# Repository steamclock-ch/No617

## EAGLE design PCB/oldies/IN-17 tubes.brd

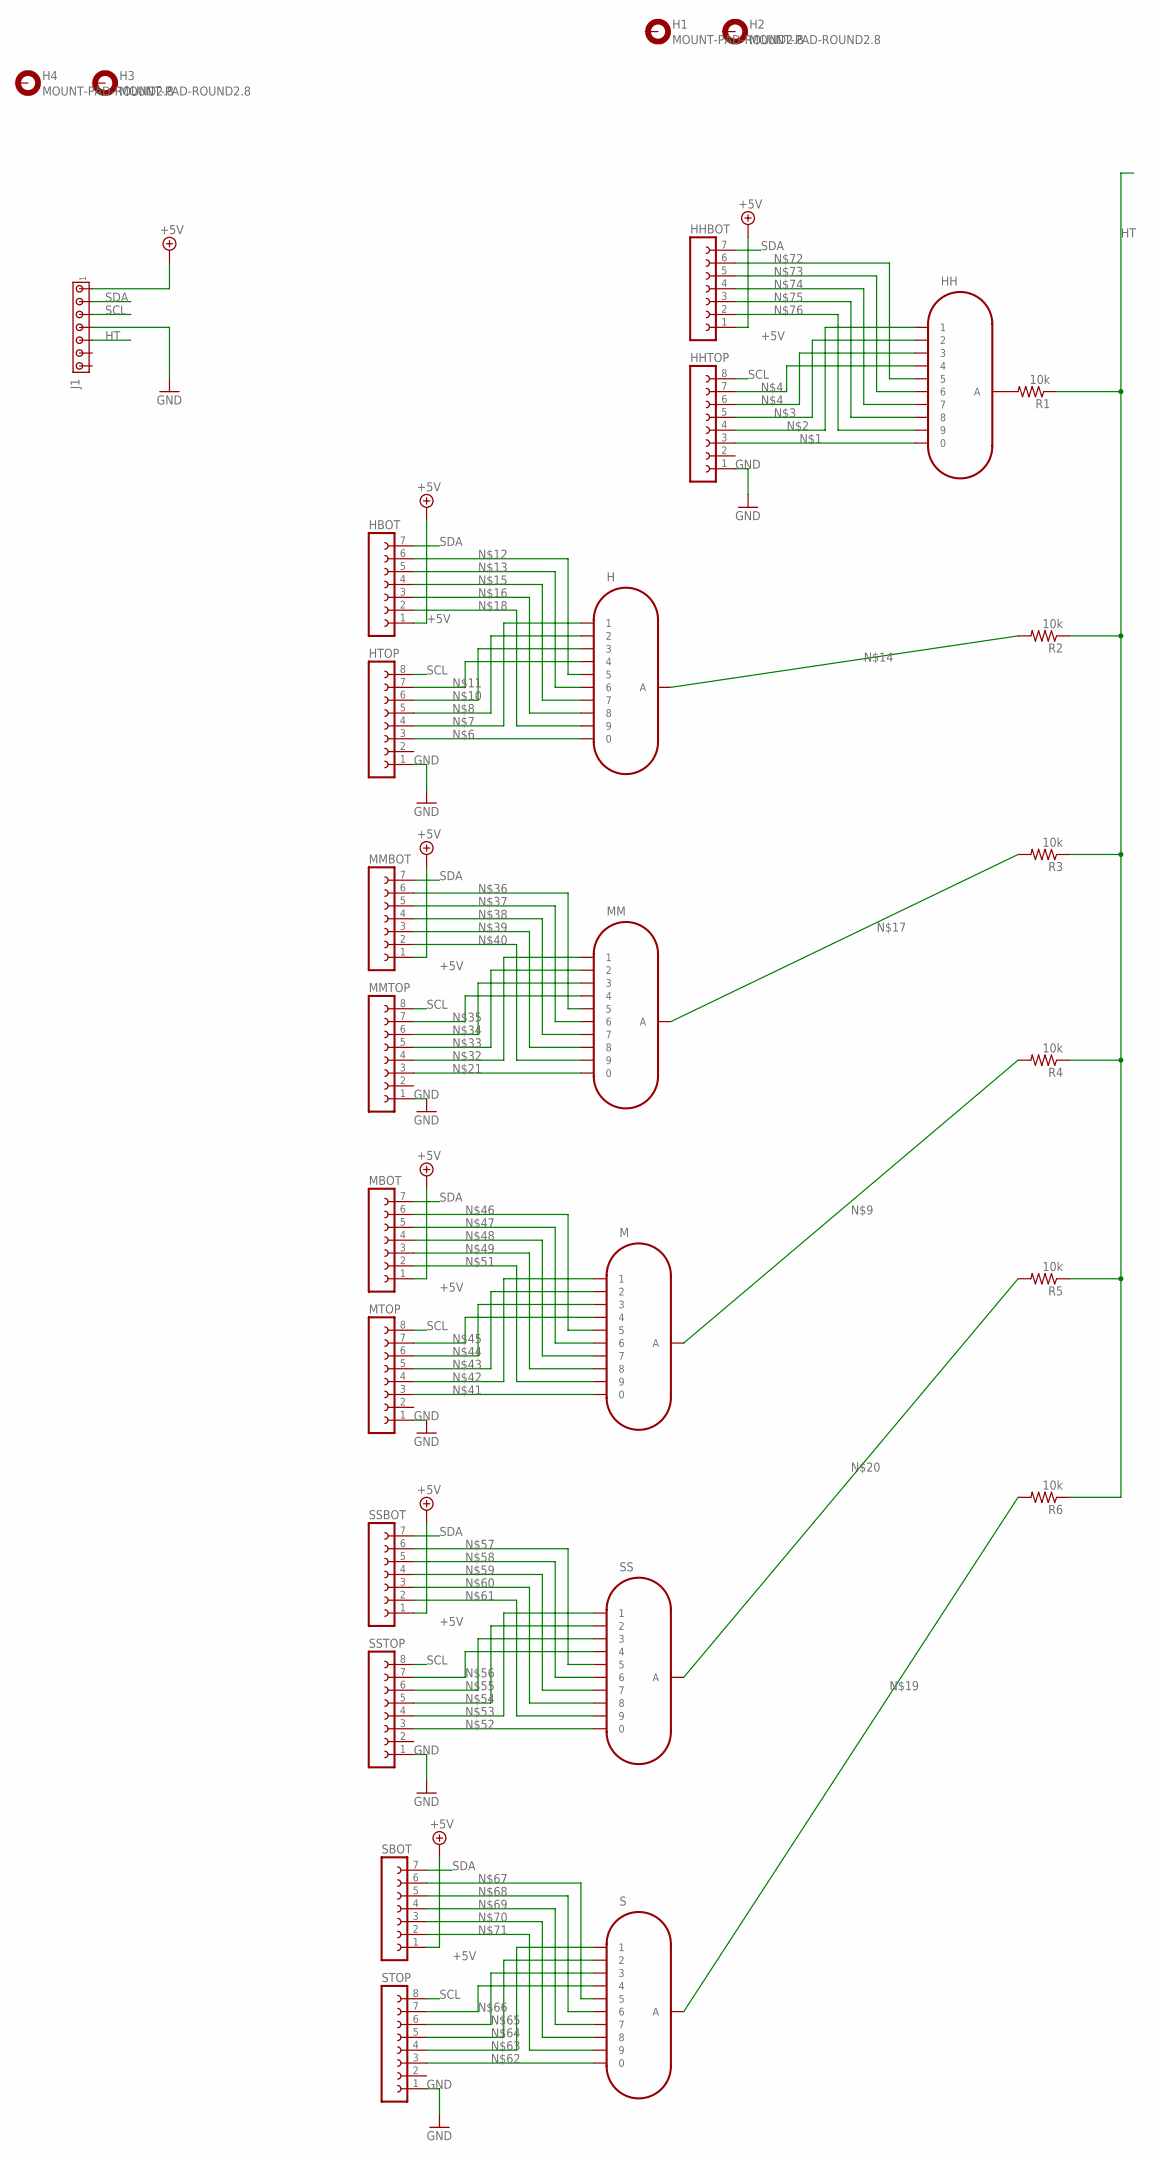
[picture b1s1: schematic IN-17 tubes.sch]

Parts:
H: IN-17
H1, H2, H3, H4: MOUNT-PAD-ROUND2.8; 2,8-PAD
HBOT: FE07-1; FE07
HH: IN-17
HHBOT: FE07-1; FE07
HHTOP: FE08-1; FE08
HTOP: FE08-1; FE08
J1: MTA07-100; 10X07MTA
M: IN-17
MBOT: FE07-1; FE07
MM: IN-17
MMBOT: FE07-1; FE07
MMTOP: FE08-1; FE08
MTOP: FE08-1; FE08
R1, R2, R3, R4, R5, R6: 10k; M0805
S: IN-17
SBOT: FE07-1; FE07
SS: IN-17
SSBOT: FE07-1; FE07
SSTOP: FE08-1; FE08
STOP: FE08-1; FE08

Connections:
+5V: HBOT.1, HHBOT.1, J1.1, MBOT.1, MMBOT.1, SBOT.1, SSBOT.1
GND: HHTOP.1, HTOP.1, J1.4, MMTOP.1, MTOP.1, SSTOP.1, STOP.1
HT: J1.5, R1.1, R2.1, R3.1, R4.1, R5.1, R6.1
unnamed: HH.0, HHTOP.3
unnamed: HH.1, HHTOP.4
unnamed: HH.2, HHTOP.5
unnamed: HH.3, HHTOP.6
unnamed: HH.4, HHTOP.7
unnamed: H.0, HTOP.3
unnamed: H.1, HTOP.4
unnamed: H.2, HTOP.5
unnamed: M.A, R4.2
unnamed: H.3, HTOP.6
unnamed: H.4, HTOP.7
unnamed: H.5, HBOT.6
unnamed: H.6, HBOT.5
unnamed: H.A, R2.2
unnamed: H.7, HBOT.4
unnamed: H.8, HBOT.3
unnamed: MM.A, R3.2
unnamed: H.9, HBOT.2
unnamed: R6.2, S.A
unnamed: R5.2, SS.A
unnamed: MM.0, MMTOP.3
unnamed: MM.1, MMTOP.4
unnamed: MM.2, MMTOP.5
unnamed: MM.3, MMTOP.6
unnamed: MM.4, MMTOP.7
unnamed: MM.5, MMBOT.6
unnamed: MM.6, MMBOT.5
unnamed: MM.7, MMBOT.4
unnamed: MM.8, MMBOT.3
unnamed: MM.9, MMBOT.2
unnamed: M.0, MTOP.3
unnamed: M.1, MTOP.4
unnamed: M.2, MTOP.5
unnamed: M.3, MTOP.6
unnamed: M.4, MTOP.7
unnamed: M.5, MBOT.6
unnamed: M.6, MBOT.5
unnamed: M.7, MBOT.4
unnamed: M.8, MBOT.3
unnamed: HH.A, R1.2
unnamed: M.9, MBOT.2
unnamed: SS.0, SSTOP.3
unnamed: SS.1, SSTOP.4
unnamed: SS.2, SSTOP.5
unnamed: SS.3, SSTOP.6
unnamed: SS.4, SSTOP.7
unnamed: SS.5, SSBOT.6
unnamed: SS.6, SSBOT.5
unnamed: SS.7, SSBOT.4
unnamed: SS.8, SSBOT.3
unnamed: SS.9, SSBOT.2
unnamed: S.0, STOP.3
unnamed: S.1, STOP.4
unnamed: S.2, STOP.5
unnamed: S.3, STOP.6
unnamed: S.4, STOP.7
unnamed: S.5, SBOT.6
unnamed: S.6, SBOT.5
unnamed: S.7, SBOT.4
unnamed: S.8, SBOT.3
unnamed: S.9, SBOT.2
unnamed: HH.5, HHBOT.6
unnamed: HH.6, HHBOT.5
unnamed: HH.7, HHBOT.4
unnamed: HH.8, HHBOT.3
unnamed: HH.9, HHBOT.2
SCL: HHTOP.8, HTOP.8, J1.3, MMTOP.8, MTOP.8, SSTOP.8, STOP.8
SDA: HBOT.7, HHBOT.7, J1.2, MBOT.7, MMBOT.7, SBOT.7, SSBOT.7

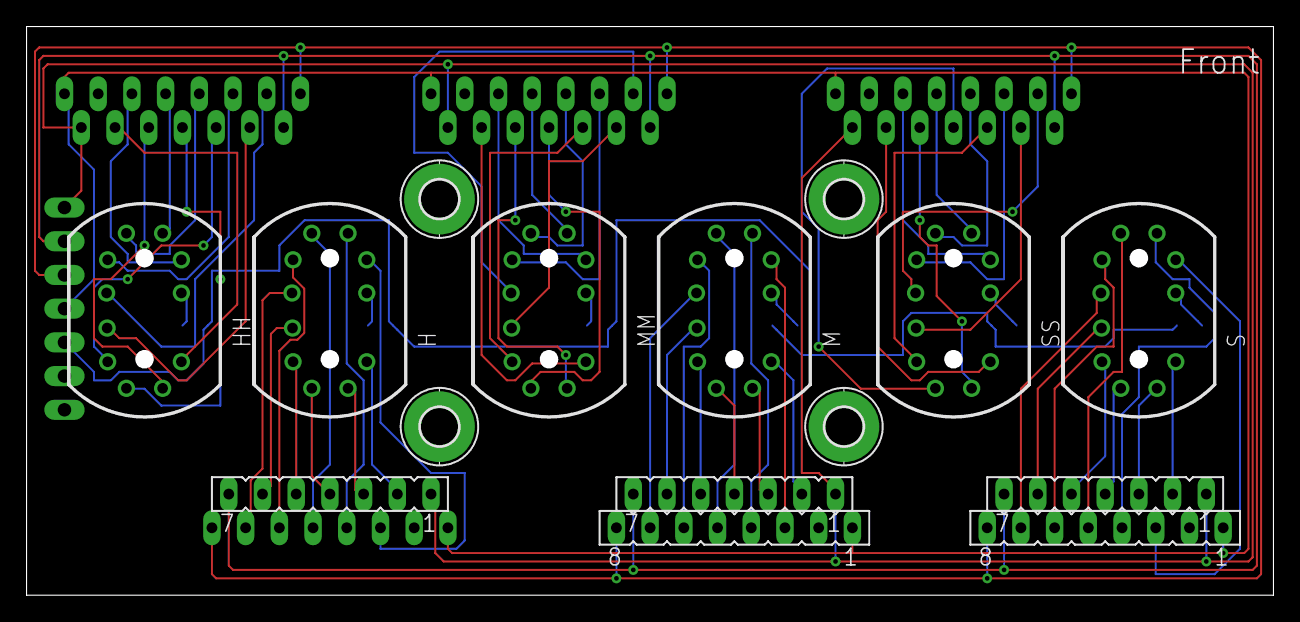
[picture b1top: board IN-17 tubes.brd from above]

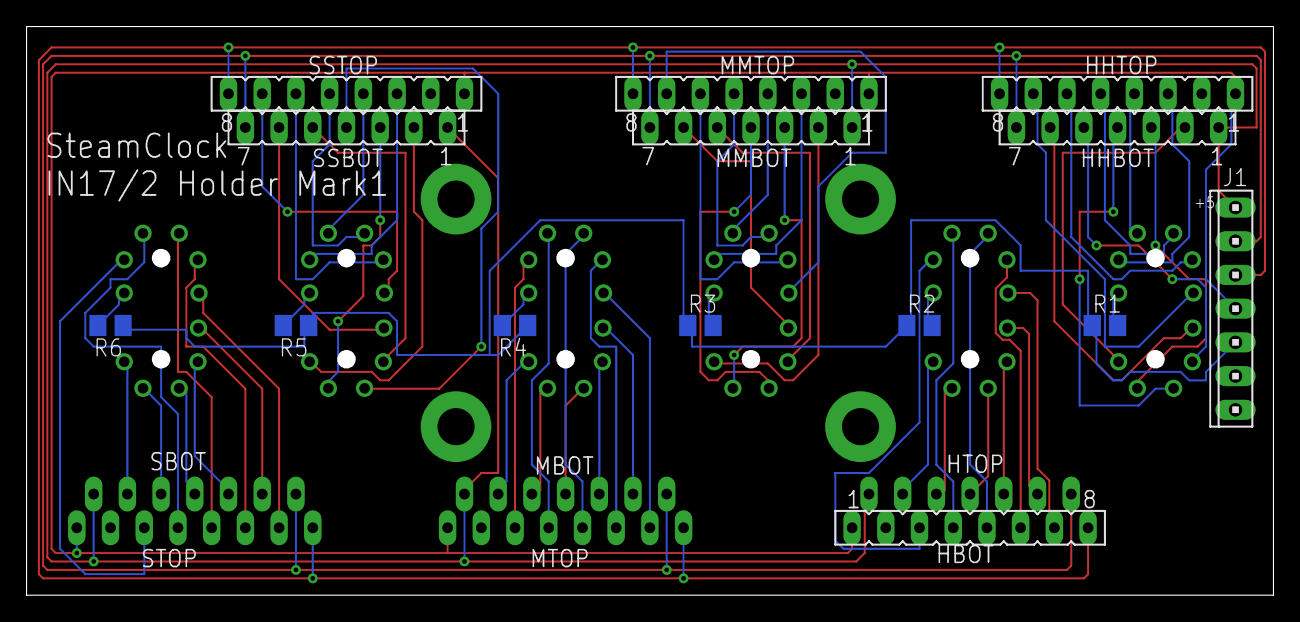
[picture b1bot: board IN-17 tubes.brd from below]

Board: 2 copper layers, 94.0 x 42.8 mm, 29 parts (14 on the bottom side), 71 nets.

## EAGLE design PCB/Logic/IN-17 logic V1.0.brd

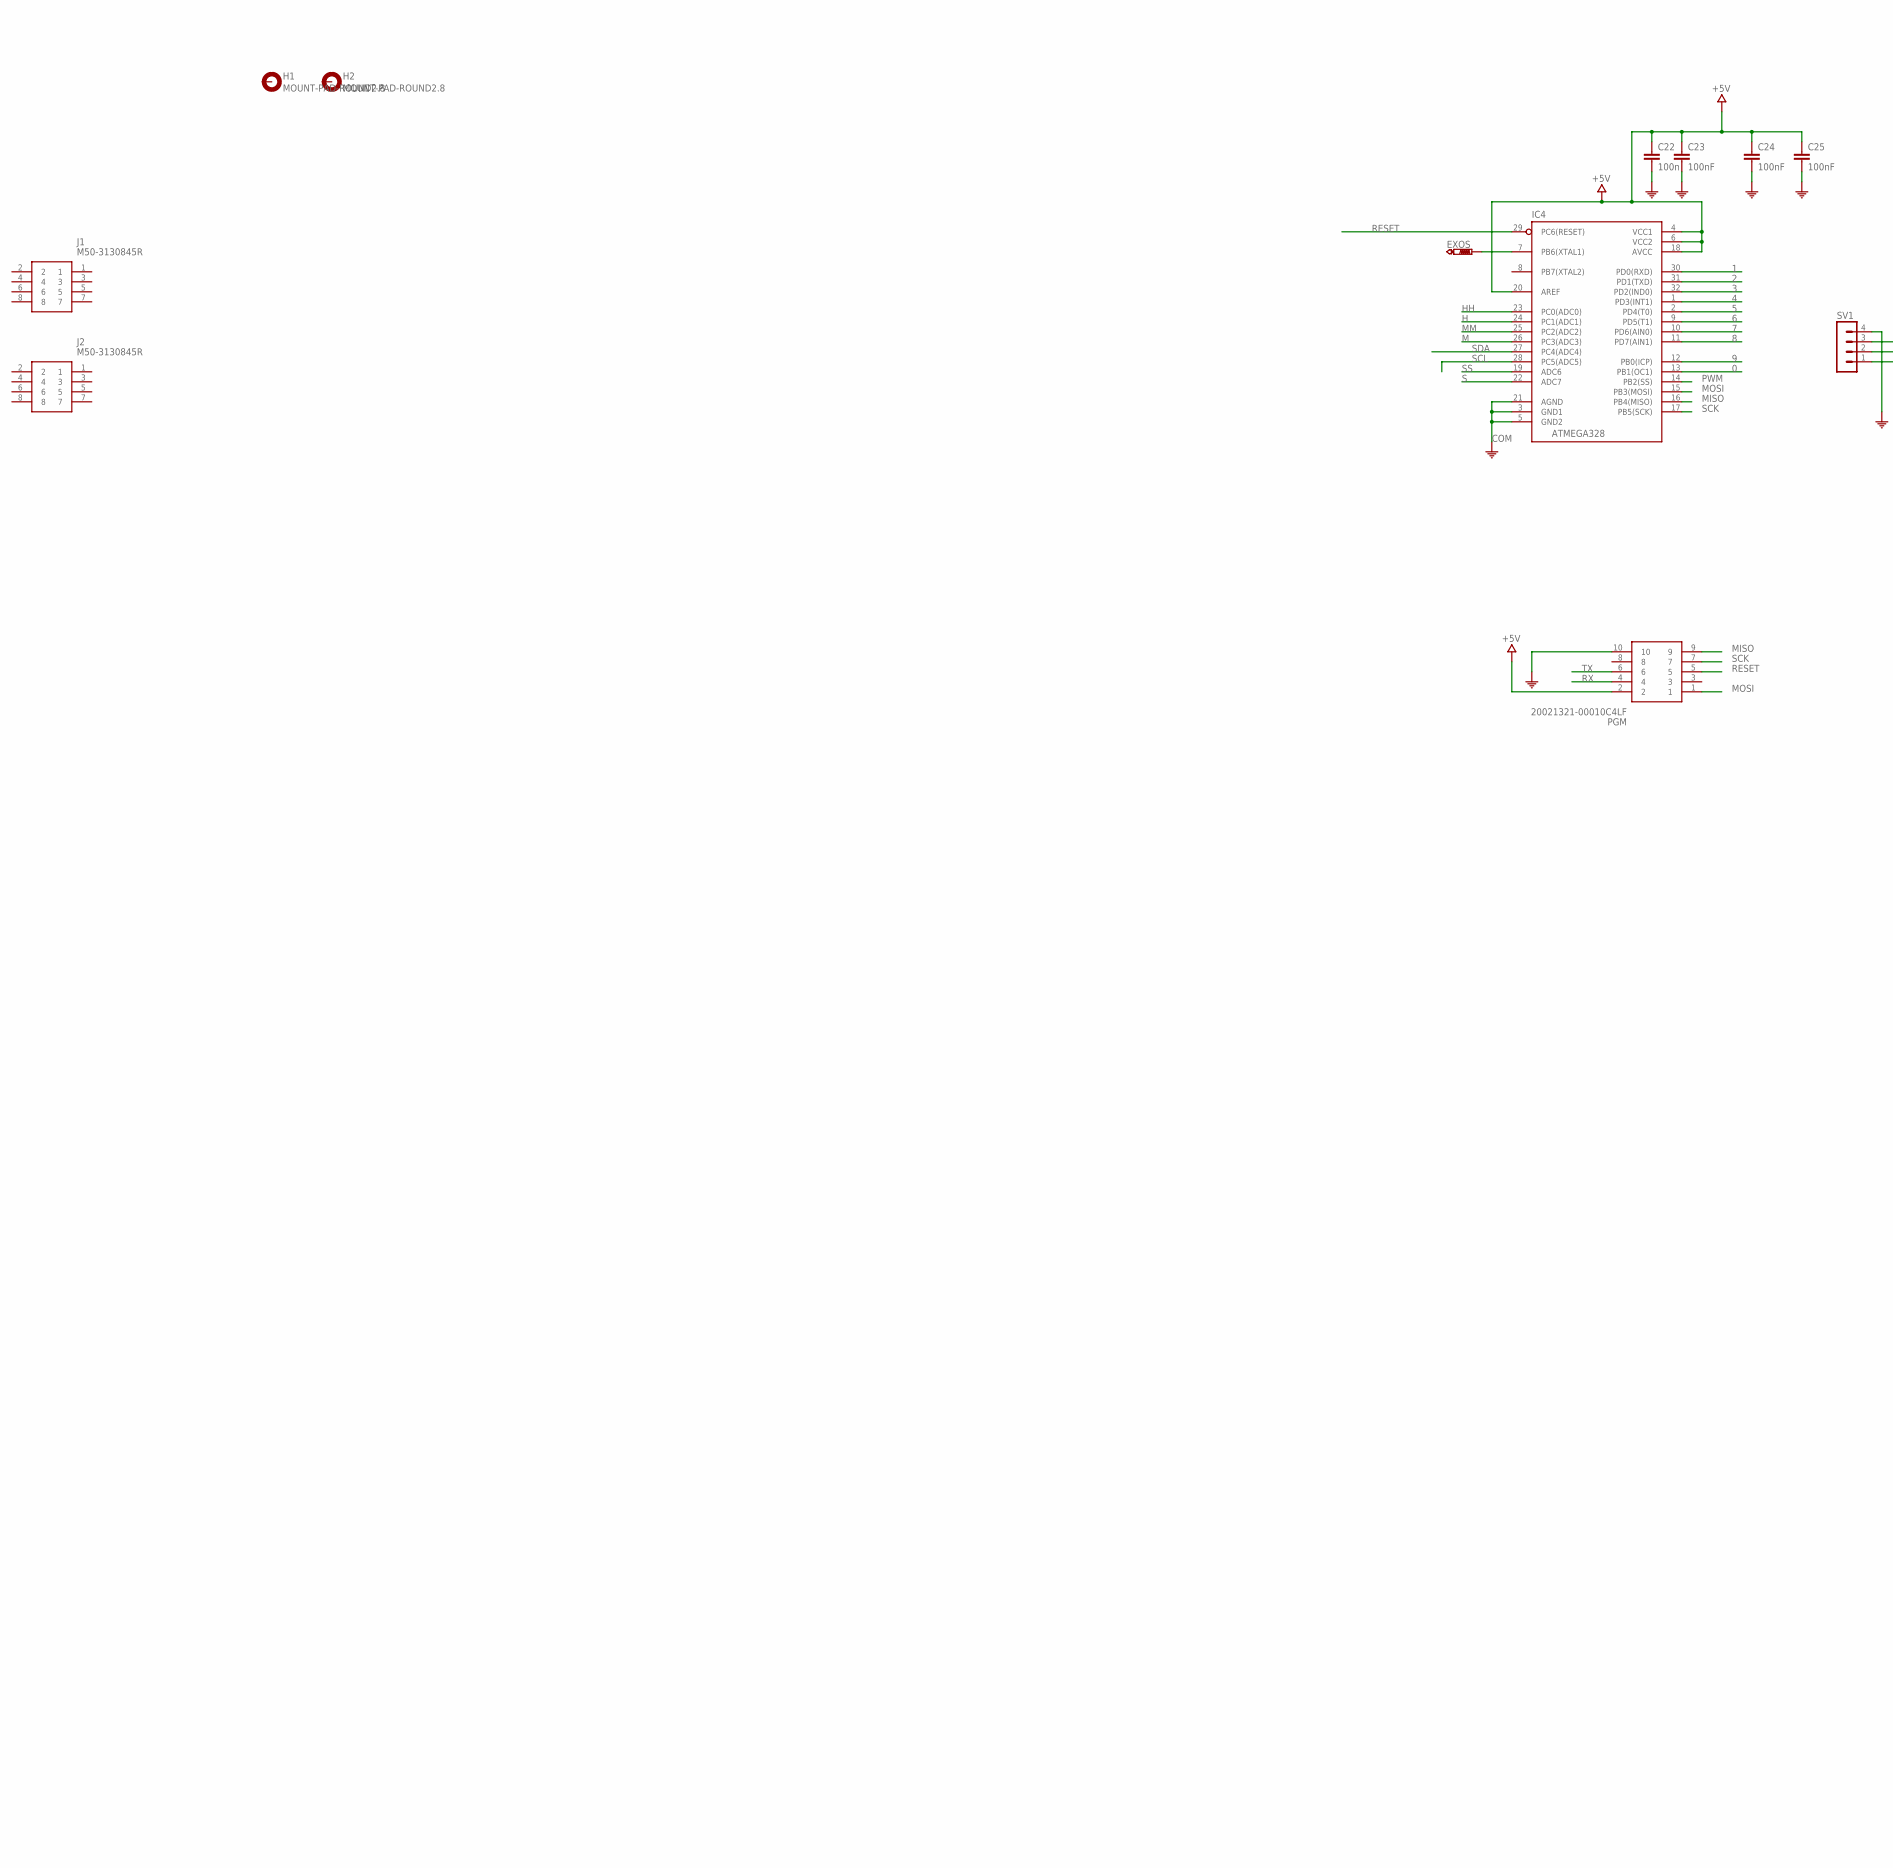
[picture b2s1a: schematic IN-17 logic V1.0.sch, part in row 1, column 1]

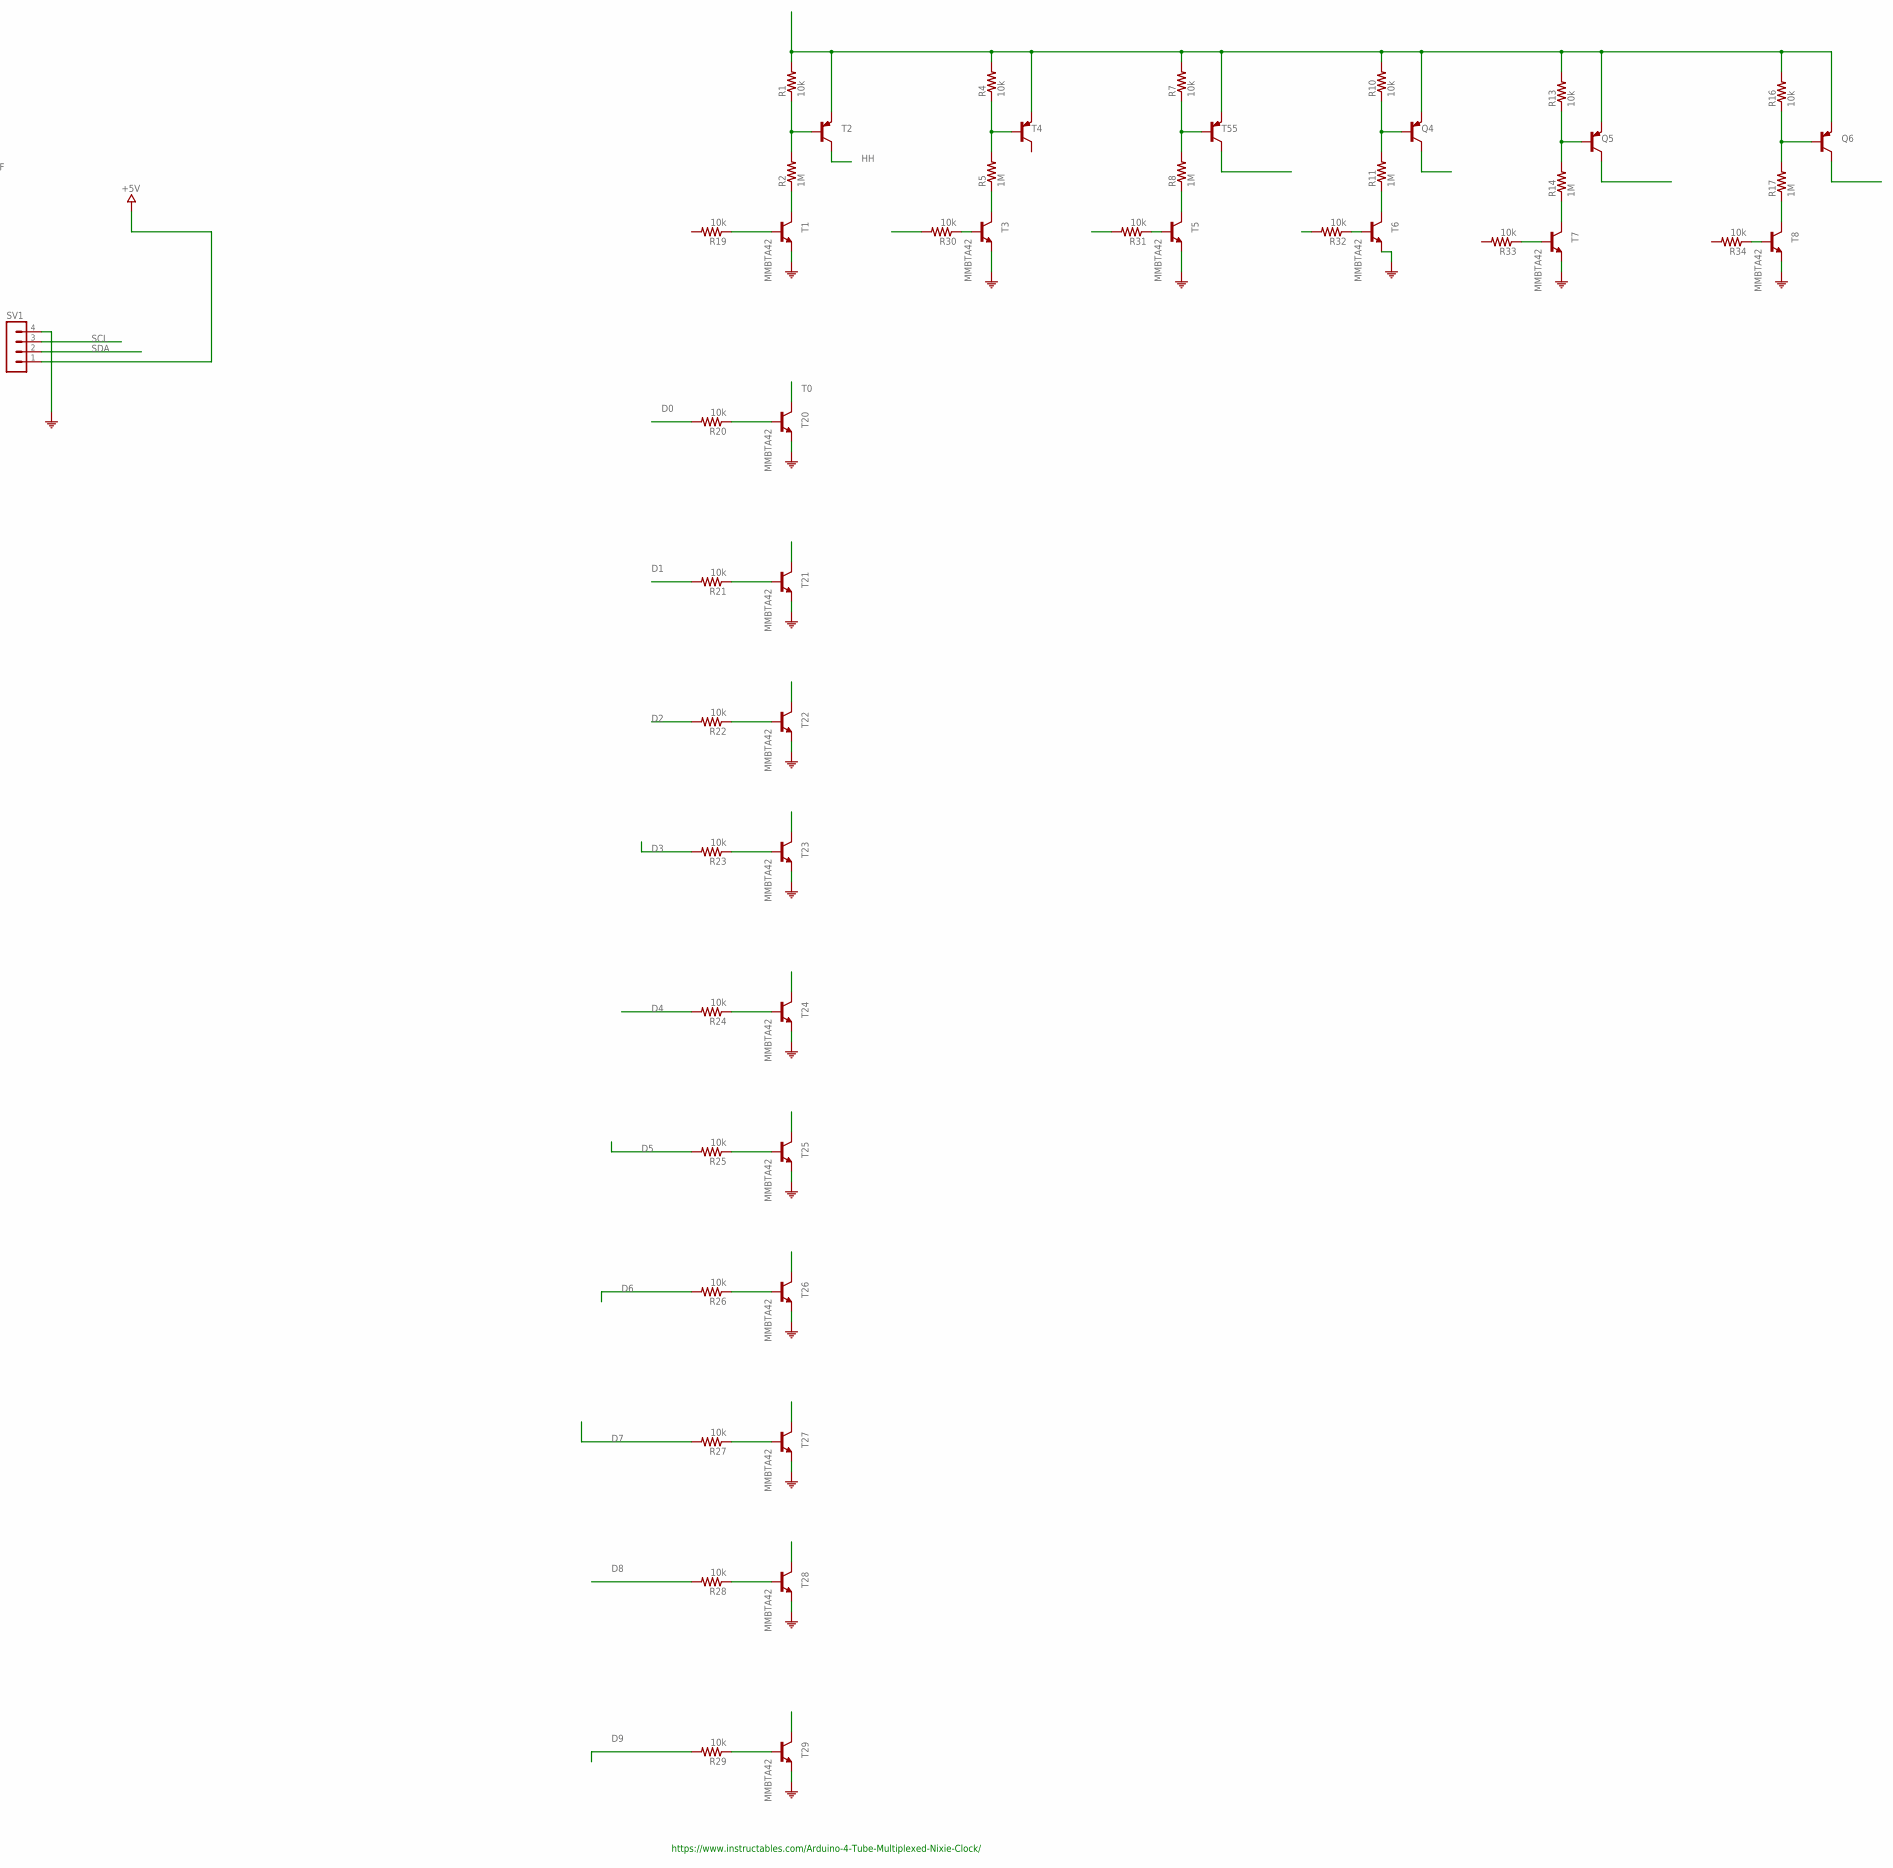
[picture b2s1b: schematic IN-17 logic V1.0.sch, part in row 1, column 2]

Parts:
C22: 100n; C0805
C23, C24, C25: 100nF; C0805
EXOS: PTR1TP09R; TP09R
H1, H2: MOUNT-PAD-ROUND2.8; 2,8-PAD
IC4: ATMEGA328; QFP032
J1, J2: M50-3130845R; M503130845R
PGM: 20021321-00010C4LF; 2002132100010C4LF
Q4, Q5, Q6: TRANSISTOR_BJT_PNP-SOT-23-BCE; SOT-23
R1, R4, R7, R10, R13, R16, R19, R20, R21, R22, R23, R24, R25, R26, R27, R28, R29, R30, R31, R32, R33, R34: 10k; R0805
R2, R5, R8, R11, R14, R17: 1M; R0805
SV1: MA04-1
T1, T3, T5, T6, T7, T8, T20, T21, T22, T23, T24, T25, T26, T27, T28, T29: MMBTA42; SOT23
T2, T4, T55: TRANSISTOR_BJT_PNP-SOT-23-BCE; SOT-23

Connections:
0: IC4.13 (PB1(OC1))
1: IC4.30 (PD0(RXD))
2: IC4.31 (PD1(TXD))
3: IC4.32 (PD2(IND0))
4: IC4.1 (PD3(INT1))
5: IC4.2 (PD4(T0))
6: IC4.9 (PD5(T1))
7: IC4.10 (PD6(AIN0))
8: IC4.11 (PD7(AIN1))
9: IC4.12 (PB0(ICP))
+5V: C22.1, C23.1, C24.1, C25.1, IC4.4 (VCC1), IC4.6 (VCC2), IC4.18 (AVCC), IC4.20 (AREF), PGM.2, SV1.1
COM: C22.2, C23.2, C24.2, C25.2, IC4.3 (GND1), IC4.5 (GND2), IC4.21 (AGND), PGM.10, SV1.4, T1.2 (E), T3.2 (E), T5.2 (E), T6.2 (E), T7.2 (E), T8.2 (E), T20.2 (E), T21.2 (E), T22.2 (E), T23.2 (E), T24.2 (E), T25.2 (E), T26.2 (E), T27.2 (E), T28.2 (E), T29.2 (E)
D0: R20.2
D1: R21.2
D2: R22.2
D3: R23.2
D4: R24.2
D5: R25.2
D6: R26.2
D7: R27.2
D8: R28.2
D9: R29.2
H: IC4.24 (PC1(ADC1))
HH: IC4.23 (PC0(ADC0)), T2.2 (C)
M: IC4.26 (PC3(ADC3))
MISO: IC4.16 (PB4(MISO)), PGM.9
MM: IC4.25 (PC2(ADC2))
MOSI: IC4.15 (PB3(MOSI)), PGM.1
unnamed: R1.1, R2.2, T2.1 (B)
unnamed: R2.1, T1.3 (C)
unnamed: Q4.3 (E), Q5.3 (E), Q6.3 (E), R1.2, R4.2, R7.2, R10.2, R13.2, R16.2, T2.3 (E), T4.3 (E), T55.3 (E)
unnamed: EXOS.TP, IC4.7 (PB6(XTAL1))
unnamed: R19.1, T1.1 (B)
unnamed: R20.1, T20.1 (B)
unnamed: R21.1, T21.1 (B)
unnamed: R22.1, T22.1 (B)
unnamed: R23.1, T23.1 (B)
unnamed: R24.1, T24.1 (B)
unnamed: R25.1, T25.1 (B)
unnamed: R26.1, T26.1 (B)
unnamed: R27.1, T27.1 (B)
unnamed: R28.1, T28.1 (B)
unnamed: R29.1, T29.1 (B)
unnamed: Q5.1 (B), R13.1, R14.2
unnamed: Q4.1 (B), R10.1, R11.2
unnamed: R7.1, R8.2, T55.1 (B)
unnamed: R4.1, R5.2, T4.1 (B)
unnamed: R5.1, T3.3 (C)
unnamed: R8.1, T5.3 (C)
unnamed: R11.1, T6.3 (C)
unnamed: R14.1, T7.3 (C)
unnamed: Q6.1 (B), R16.1, R17.2
unnamed: R17.1, T8.3 (C)
unnamed: R34.1, T8.1 (B)
unnamed: R33.1, T7.1 (B)
unnamed: R32.1, T6.1 (B)
unnamed: R31.1, T5.1 (B)
unnamed: R30.1, T3.1 (B)
PWM: IC4.14 (PB2(SS))
RESET: IC4.29 (PC6(RESET)), PGM.5
RX: PGM.4
S: IC4.22 (ADC7)
SCK: IC4.17 (PB5(SCK)), PGM.7
SCL: IC4.28 (PC5(ADC5)), SV1.3
SDA: IC4.27 (PC4(ADC4)), SV1.2
SS: IC4.19 (ADC6)
T0: T20.3 (C)
TX: PGM.6

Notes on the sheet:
https://www.instructables.com/Arduino-4-Tube-Multiplexed-Nixie-Clock/

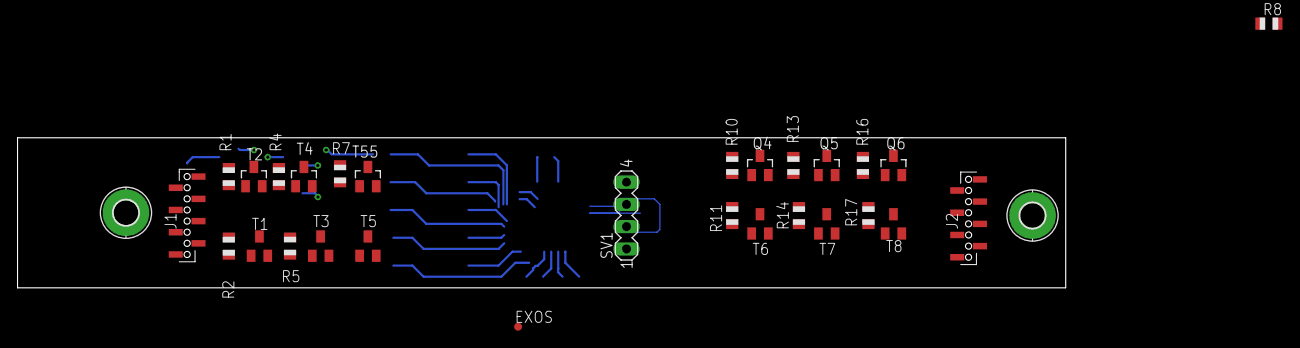
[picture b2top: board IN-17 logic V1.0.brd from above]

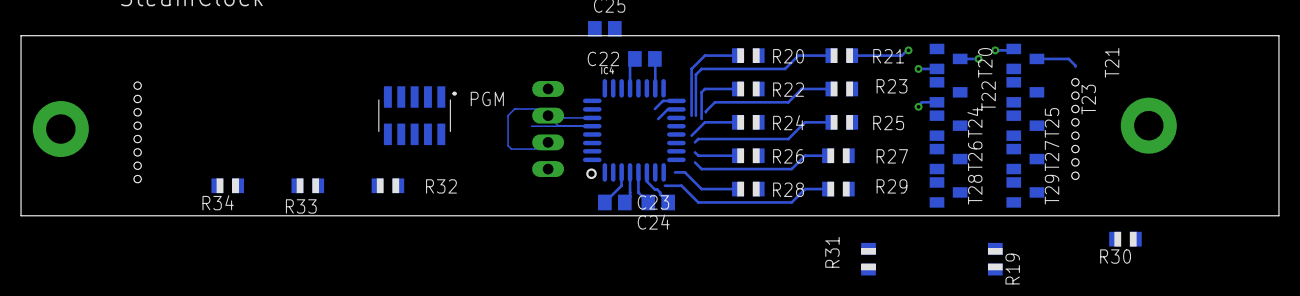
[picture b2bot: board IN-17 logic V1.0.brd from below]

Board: 4 copper layers, 119.7 x 17.1 mm, 62 parts (32 on the bottom side), 39 nets.

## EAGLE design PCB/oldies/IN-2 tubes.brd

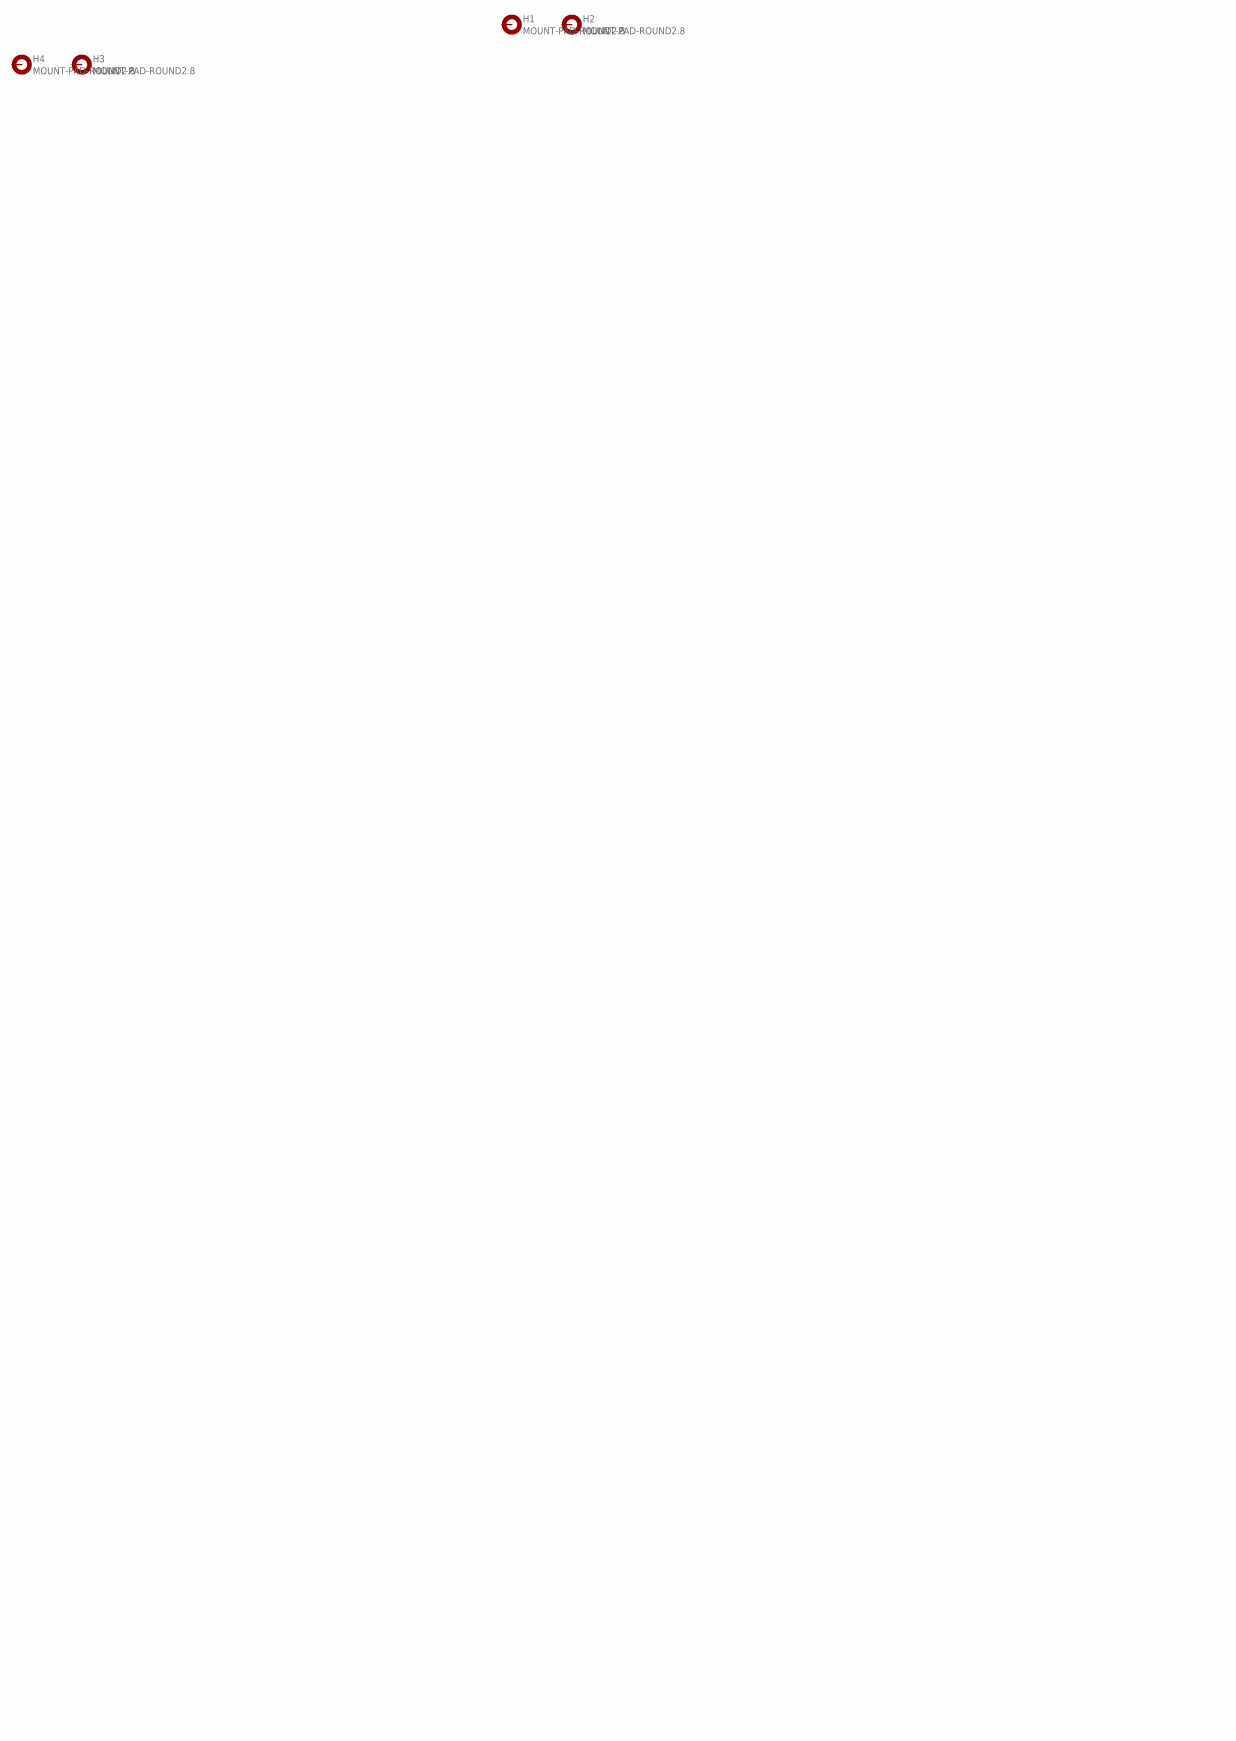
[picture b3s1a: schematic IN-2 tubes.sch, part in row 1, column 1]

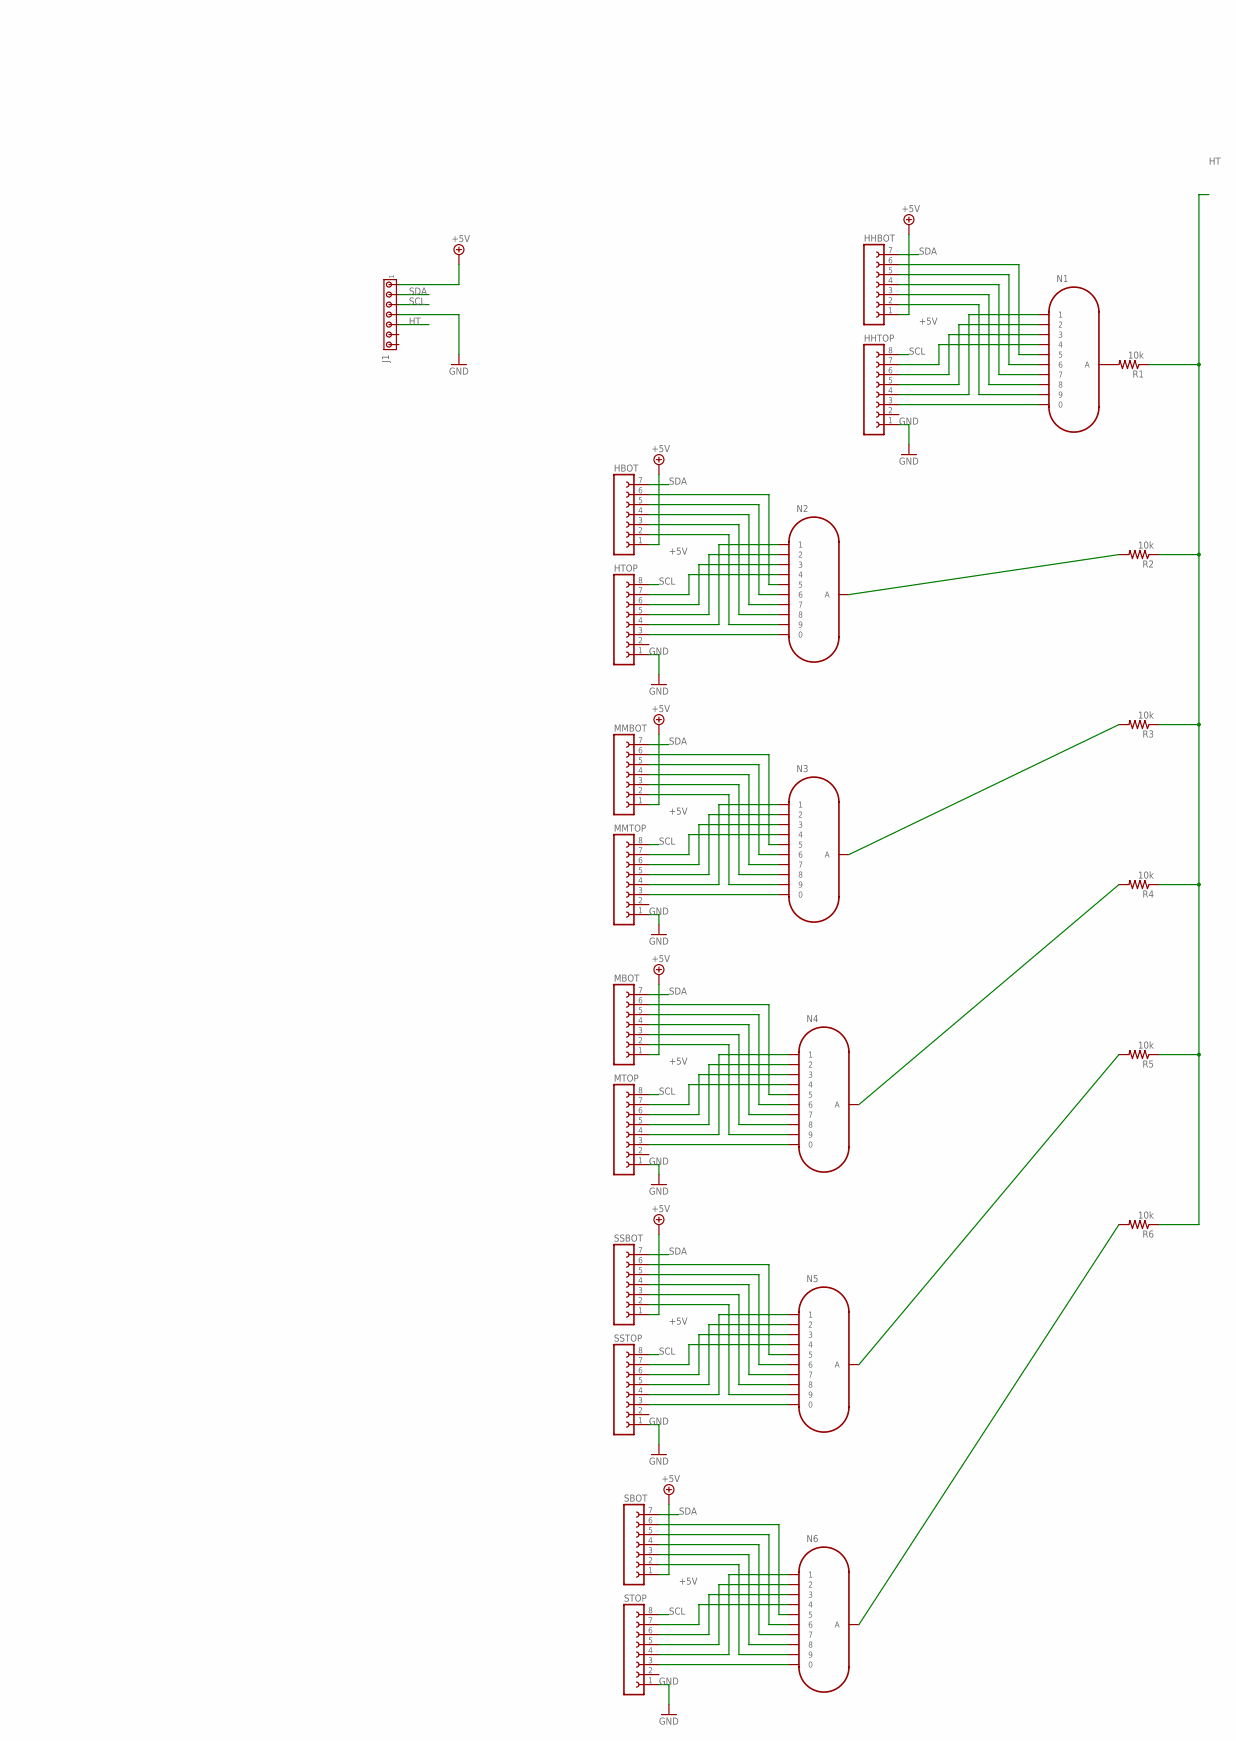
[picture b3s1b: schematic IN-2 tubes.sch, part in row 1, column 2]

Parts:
H1, H2, H3, H4: MOUNT-PAD-ROUND2.8; 2,8-PAD
HBOT: FE07-1; FE07
HHBOT: FE07-1; FE07
HHTOP: FE08-1; FE08
HTOP: FE08-1; FE08
J1: MTA07-100; 10X07MTA
MBOT: FE07-1; FE07
MMBOT: FE07-1; FE07
MMTOP: FE08-1; FE08
MTOP: FE08-1; FE08
N1, N2, N3, N4, N5, N6: IN-2; IN-8
R1, R2, R3, R4, R5, R6: 10k; M0805
SBOT: FE07-1; FE07
SSBOT: FE07-1; FE07
SSTOP: FE08-1; FE08
STOP: FE08-1; FE08

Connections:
+5V: HBOT.1, HHBOT.1, J1.1, MBOT.1, MMBOT.1, SBOT.1, SSBOT.1
GND: HHTOP.1, HTOP.1, J1.4, MMTOP.1, MTOP.1, SSTOP.1, STOP.1
HT: J1.5, R1.1, R2.1, R3.1, R4.1, R5.1, R6.1
unnamed: HHTOP.3, N1.0
unnamed: HHTOP.4, N1.1
unnamed: HHTOP.5, N1.2
unnamed: HHTOP.6, N1.3
unnamed: HHTOP.7, N1.4
unnamed: HTOP.3, N2.0
unnamed: HTOP.4, N2.1
unnamed: HTOP.5, N2.2
unnamed: N4.A, R4.2
unnamed: HTOP.6, N2.3
unnamed: HTOP.7, N2.4
unnamed: HBOT.6, N2.5
unnamed: HBOT.5, N2.6
unnamed: N2.A, R2.2
unnamed: HBOT.4, N2.7
unnamed: HBOT.3, N2.8
unnamed: N3.A, R3.2
unnamed: HBOT.2, N2.9
unnamed: N6.A, R6.2
unnamed: N5.A, R5.2
unnamed: MMTOP.3, N3.0
unnamed: N1.A, R1.2
unnamed: MMTOP.4, N3.1
unnamed: MMTOP.5, N3.2
unnamed: MMTOP.6, N3.3
unnamed: MMTOP.7, N3.4
unnamed: MMBOT.6, N3.5
unnamed: MMBOT.5, N3.6
unnamed: MMBOT.4, N3.7
unnamed: MMBOT.3, N3.8
unnamed: MMBOT.2, N3.9
unnamed: MTOP.3, N4.0
unnamed: MTOP.4, N4.1
unnamed: MTOP.5, N4.2
unnamed: MTOP.6, N4.3
unnamed: MTOP.7, N4.4
unnamed: MBOT.6, N4.5
unnamed: MBOT.5, N4.6
unnamed: MBOT.4, N4.7
unnamed: MBOT.3, N4.8
unnamed: MBOT.2, N4.9
unnamed: N5.0, SSTOP.3
unnamed: N5.1, SSTOP.4
unnamed: N5.2, SSTOP.5
unnamed: N5.3, SSTOP.6
unnamed: N5.4, SSTOP.7
unnamed: N5.5, SSBOT.6
unnamed: N5.6, SSBOT.5
unnamed: N5.7, SSBOT.4
unnamed: N5.8, SSBOT.3
unnamed: N5.9, SSBOT.2
unnamed: N6.0, STOP.3
unnamed: N6.1, STOP.4
unnamed: N6.2, STOP.5
unnamed: N6.3, STOP.6
unnamed: N6.4, STOP.7
unnamed: N6.5, SBOT.6
unnamed: N6.6, SBOT.5
unnamed: N6.7, SBOT.4
unnamed: N6.8, SBOT.3
unnamed: N6.9, SBOT.2
unnamed: HHBOT.6, N1.5
unnamed: HHBOT.5, N1.6
unnamed: HHBOT.4, N1.7
unnamed: HHBOT.3, N1.8
unnamed: HHBOT.2, N1.9
SCL: HHTOP.8, HTOP.8, J1.3, MMTOP.8, MTOP.8, SSTOP.8, STOP.8
SDA: HBOT.7, HHBOT.7, J1.2, MBOT.7, MMBOT.7, SBOT.7, SSBOT.7

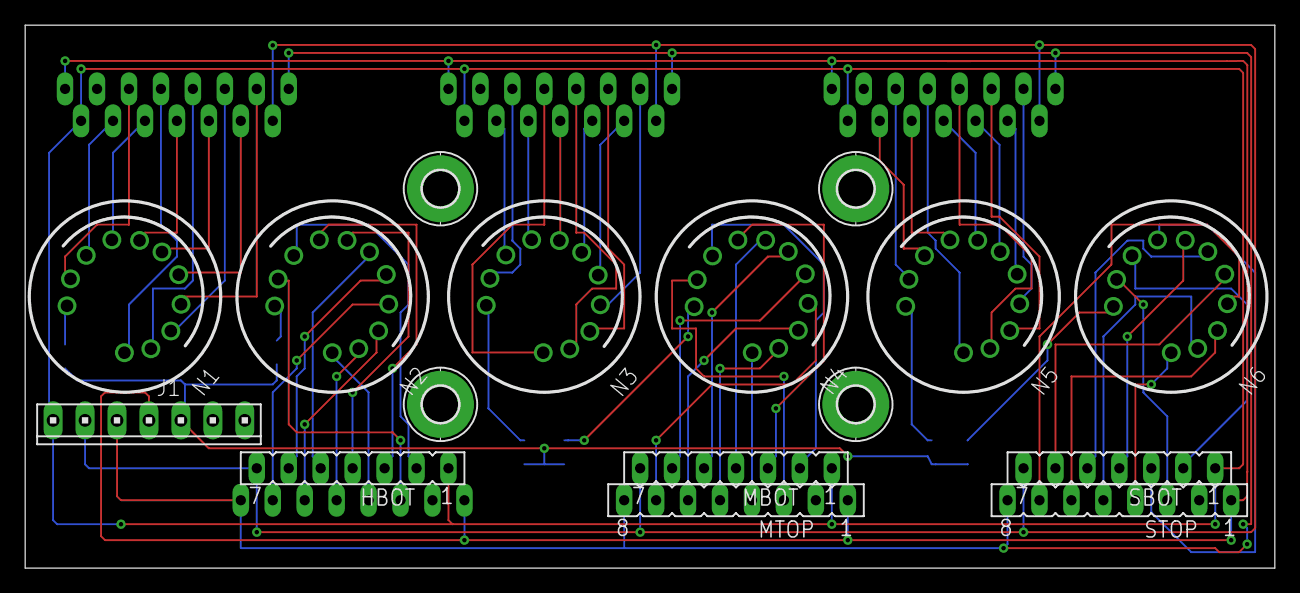
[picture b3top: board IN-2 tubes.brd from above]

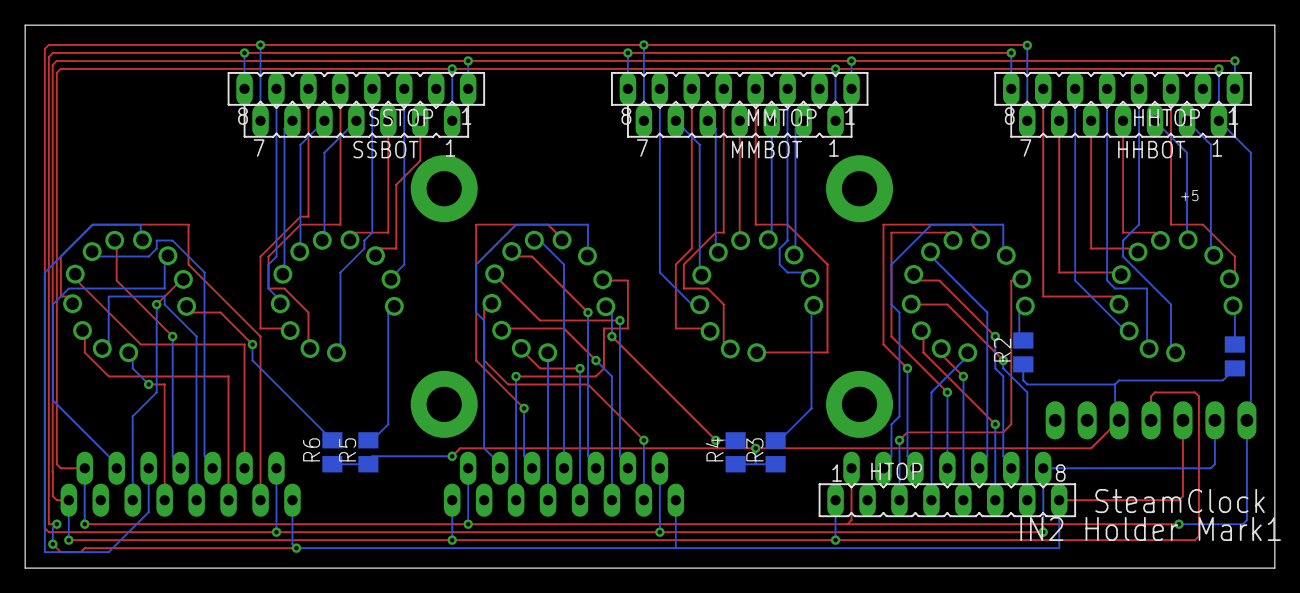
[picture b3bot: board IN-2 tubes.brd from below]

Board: 2 copper layers, 99.4 x 43.2 mm, 29 parts (13 on the bottom side), 71 nets.
